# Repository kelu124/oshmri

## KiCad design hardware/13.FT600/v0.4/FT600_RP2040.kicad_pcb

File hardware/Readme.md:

# OSHMRI

## Concept

## Design

* [Source files](common_board/)

## PMODs specs

### AFE #1 (ADC)

* 1 dual PMOD, 12ADCbits+1clk + 1SPI (without MISO): based on the AD8331+ADC+DAC from https://github.com/kelu124/lit3rick/ (altium source in hardware folder) . Connector in: SMA, with MD0100 to protect. Possible elements:
  * AD8331
  * ADC: AD9629BCPZ-65: 12bits,
  * DAC: MCP4812-E/MS

### Ultrasound PULSER

* Only logic through PMOD: 
  * positivepulse, negativepulse, damp.
  * Expose remaining IOs on a 2.54" rail on the PMOD board (with 3.3V and GND as well)
* External GPIOs for +HV, -HV, GND. 
* Internal : 
  * Positive: 3.3V -> 5V booster ; 
  * Negative: -5V rail for example (not mandatory if simpler exists) https://www.mouser.fr/new/texas-instruments/ti-lm27761-voltage-inverter/
  * Design similar to the HV connector on lit3rick (jumpers to connect 5V to HV and -5V to -HV 
* Connector out: SMA.
* Ref design : https://www.arrow.com/en/reference-designs/high-voltage-pulser-circuit-using-the-md1213-and-tc6320-100v-ultrasound-pulser/4e167e0bac7f3ae2900d35260e7663cc 

### GRADIENTS PMOD

* Objective is to be able to produce 4 waveformes similar to those: https://github.com/kelu124/oshmri/tree/main/hardware#gradients
* 4 DACs outputs, 10bits (or more) : https://www.analog.com/media/en/technical-documentation/data-sheets/ltc2634.pdf
* there are already schematics and altium sources at
https://www.mouser.fr/ProductDetail/Analog-Devices/DC1488A-A?qs=ytflclh7QUXpxdBLSaXWCQ%3D%3D ( the only thing would be for outputs to be between -Vref and +Vref - using possibly a max1721 for neg. 3.3v ).

### !! NOT FOR THIS ONE - AFE #2 (SDR)
* Using the SDR chips: https://pbs.twimg.com/media/FLk5M53XsAIO2Jr?format=jpg&name=large path for 0-30MHz - IOs on the PMOD would be IO0..3 and the 4 SPI signals (for the DAC coupled to AD8331)
* Input as SMA, going to MD0100, AD8331, then MSI001, MSI2500, usb output.

# Specs

## Overview

The basic schematic of an MRI system is shown in Figure 1. The MRI spectrometer is responsible for playing out the RF and gradient pulses and receiving the MR signal and manages logic signals.

Overall strategy is: First make it work, then make it nice (=cheaper & more open source). 

Low cost (500eur) design for educational purposes and low budget. 3 typical freqs:

* 0.05 T - central freq 2.15MHz, 20kHz to 50kHz bandwidth
* 0.1  T - central freq 4 MHz, up to 500kHz bandwidth
* 0.3  T - central freq 13MHz, up to 500kHz bandwidth
* 0.5  T - central freq 21 MHz, up to 500kHz bandwidth

While it is definitely appealing to a have a broad application range for the spectrometer. An initial application goal would be DC-64MHz (up to B0=1.5T) or even lower. The first open source hardware MR systems will be low field (B0 inf to 0.5T, f~DC-21MHz). 

## Requirements

### Overall 

Maybe it's good for me to share what (hardware wise) the 'ideal' spectrometer requirements would look:

* 1xRF transmit channel - 16bit+
  * Voltage range: up to 1Vpp	
  * Sampling speed and nb bits: `@what@` -> _flexible_
  * Duration of transmit: up to 10ms, typically shorter.

#### Transmit

The minimum number of transmission channels is four (1x Tx RF, 3x Gradients). Is a higher number (how many?) in transmission channels desirable? e.g. for:
* broad BW excitation
* spatial encoding

* 4x kHz gradients transmits - (~250 kHz) ~20 bit dacs for the gradient waveforms
  * 4 SPIs ?

#### Receive

* 1x RF receive - Central freq @2, 4, 13 or 21Mhz. 
  * _BW on the Rx side nice-to-have would be 500 kHz, practically I think 50 kHz would satisfy most needs_
  * ADC 16bit 
  * Duration of acquisition : up to 20ms
  * Gain for acquisition : 0 to 30dB
* Ability to daisy chain for multiple receive channels (up to e.g. 16 or 32 RX channels would be great in the future to get an SNR boost)
* High frequency and phase stability (accurate and stable timings below 1us (preferably much less) jitter). One of the most important things in MR is the timing, both for transmission and reception (please check the IPSO part of the bruker hardware manual that I have attached). 

A higher number of receive channels increases SNR. 16-32 receive channels desirable.

### ADC

The bit depth varies on the SNR that is expected. With a human extremity low field system of 50 mT 14 bits for raw signal may be a good start. On the opposite side of the range, I have seen high field systems using 20 bits demodulated signal.

### IOs

GPIO pins to communicate with peripherals for for instance amplifier deblanking. Logic:
* Blanking
* Sampling on
* Gradients On
* Pulse On

### Other ports ?

* USB port 
* Ethernet port
* HDMI/VGA  Displayportport (HDMI/VGA)
* GPIO port
* Motor interface
* Debug Port (Rs232/422)
* PCI?
* SFP ports (Might be overkill but for the mid cost version, it can boost many operations. Also, low cost versions can be used for the slower communications/instructions when interfacing between imaging room and the spectrometer)

## Storage

* Images are 256x256*256 or above, 16bits imaginary
  * 64MB / image
  * 256kB / plane

## Ideas

PMODs! 8 IOs = loads

* Transmit: AD9102 - 20 EUR
  * 14 bits, 180Msps, 4096 word pattern
  * @180msps, 4096pts = 22us.

## RF

### Overall

On the RF image, green represents acquisitions. Do you confirm that's for the 3 ADCs?

I agree that might be a bit confusing. Green is not the acquisition, it is the gradient. There are three gradients for different purposes and the acquisition (sampling) is in between two gradients (orange and green in TSE sequence description.png)) and during x gradient (blue) at 10ms, 20ms, 30ms etc. This is a single line of the MR image and this pulse sequence is being repeated multiple times (e.g. 128 or 256). The lengths of the pulse sequence is called TR repetition time. A better understanding is here (check fast spin echo and the signal location, thats where ADC sampling kicks in). There is only one ADC for sampling the receiving signal per RF receive coil channel. One thing that is being done and that boost SNR is to have multiple RF receiver channels. Thats why my previous comment to have an option to add or connect more Rx channels later would be great. For transmission at the moment 1 RF channel is sufficient. More would be interesting, but more from research perspective and at the moment 1 is sufficieent. For the gradients we need 3Tx. Forget about the 64MHz for the moment (we dont have 1.5T magnets for the OSH stuff anyway at the moment) if its too complicated, we can focus on the low field MR systems up to 0.5T (So in total 1xRF @ 1 or 2MHz - 22MHz. ven up to 0.2T or 0.3T, ca 13MHz would be fine).

### Gradients

## Blocks

### RF acquisitions

* And how long does it take? I'm reading roughly 10ms acquisitions. _The sinc pulse that is shown is for transmission, which is around 10ms. They can be also shorter. For the acquisition it will be typically shorter (e.g. in the TSE sequence image that I have sent you it is around 5ms, but it could be higher e.g. 20ms (see also docs from answer below))_
* At 64Msps that's quite some data (64*10*1000 points). _Yes MRI scans produce quite some data, but there are also some tricks. Have a look here: http://mri-q.com/receiver-bandwidth.html and here: [bandwidthinmrisiemens.pdf](pdfs/bandwidthinmrisiemens.pdf)._

### Gradients

* On the gradient waveforms, do you confirm that's more or less constants (ie square pulses)? _The gradient waveforms are mostly trapezoidal. There are some more fancy things with arbitrary gradient waveforms, but for classical MR that would be ok._

### Block pulses

* I trust the Block pulse is a gate pulse - what is its lengths? A ms or so ? _There will be a pulse to gate the RF power amplifier and the TR switches. The pulse lengths depends on the RF pulse lenghts. So sth like 1-5ms._

## Competition

'It has shortcomings too. I think one of the reasons we've decided to work with it now is that it is being adopted across multiple sites so that the development burden is shared.'

## To sort

* Thesis for the development of a https://upcommons.upc.edu/handle/2117/90394?locale-attribute=en FT600 +SDR
   * https://www.maximintegrated.com/en/products/analog/data-converters/analog-front-end-ics/MAX5866.html

* AD8339 better ? DC to 50MHz

## Ideas:

#### Core PMODs

* Board central + extesions
  * xPMOD DAC for pulse (MRI)
  * 1PMOD for pulse (ultrasound)
  * 2PMOD ADC for acquisition - onboard + gain -- common
  * 1PMOD 4 Gradients (MRI)
  * 1PMOD for HV (ultrasound + external alim)
* Comm
  * 2PMOD for USB3: FT600
  * 2PMOD for USB3: CH569
* Comm output:
  * Msi001 Msi2500 for USB

#### Backlog for PMODS

* __ACQ__: 1 dual PMOD, 12ADCbits+1clk + 1SPI (without MISO): based on the AD8331+ADC+DAC from https://github.com/kelu124/lit3rick/ . Connector in: SMA, with MD0100 to protect.
* __USPULSE__: 1 single PMOD: for the concept here: https://www.arrow.com/en/reference-designs/high-voltage-pulser-circuit-using-the-md1213-and-tc6320-100v-ultrasound-pulser/4e167e0bac7f3ae2900d35260e7663cc . Only logic through PMOD. External GPIOs for +HV, -HV, GND. Connector out: SMA.
* __4GRADs__ 1 PMOD: 4 DACs outputs, 10bits (or more) to start with. MCP48CMB24-E/ML could work, maybe? Objective is to be able to produce 4 waveformes similar to those: https://github.com/kelu124/oshmri/tree/main/hardware#gradients
* __SDR ACQ__: https://pbs.twimg.com/media/FLk5M53XsAIO2Jr?format=jpg&name=large path for 0-30MHz - IOs on the PMOD would be IO0..3 and the 4 SPI signals (for the DAC coupled to AD8331) Input as SMA, going to MD0100, AD8331, then MSI001, MSI2500, usb output.

## Competition

Commercially available spectrometers (>2000€)
* Kea 2	
* Crimson TNG	
* EVO	
* Redstone	
* iSpin-NMR	
* Medusa	
* Pure Devices	
* TekMag	
* RS2D	
* Ettus USRP SDR
*  Aspect Imaging – AMOS

## Pulser

## Resources:

## First set

* https://www.researchgate.net/publication/232935201_A_digital_receiver_module_with_direct_data_acquisition_for_magnetic_resonance_imaging_systems
  * AD9852 DDS + direct sampling
* https://www.researchgate.net/publication/231108694_A_single-board_NMR_spectrometer_based_on_a_software_defined_radio_architecture
* https://www.researchgate.net/publication/51189854_A_versatile_pulse_programmer_for_magnetic_resonance_imaging
* https://www.researchgate.net/publication/265176277_Comparison_of_Analog_and_Digital_Transceiver_Systems_for_MR_Imaging

## Other

* Liang X, A digital magnetic resonance imaging spectrometer using digital signal processor and field programmable gate array. DOI: 10.1063/1.4803007
* Takeda K, A highly integrated FPGA-based nuclear magnetic resonance spectrometer, DOI: 10.1063/1.2712940
* Zhao C, Design of a digital spectrometer for the MRI system, PMID: 17672364
* Hasselwander, Christopher J., Zhipeng Cao, and William A. Grissom. "gr-MRI: A software package for magnetic resonance imaging using software defined radios." Journal of Magnetic Resonance 270 (2016): 47-55.
* Layton, Kelvin J., et al. "Pulseq: A rapid and hardware‐independent pulse sequence prototyping framework." Magnetic resonance in medicine 77.4 (2017): 1544-1552.
* Ravi, Keerthi Sravan, et al. "Pulseq-Graphical Programming Interface: Open source visual environment for prototyping pulse sequences and integrated magnetic resonance imaging algorithm development." Magnetic resonance imaging 52 (2018): 9-15.

# Software reqs

There are a couple of existing possibilities to enable this:
* Python based backend programming. 
* Extend Pulseq framework Ref, then GPI Ref or other higher level sequence programming packages can be used for easy programming of pulse sequences. 
* Compatibility with gnuRadio (https://www.gnuradio.org/), then the grMRI framework can be used and extend to program pulse sequences Ref. 

# Qui ?

* Lukas W
* Lionel B
* Tom OR

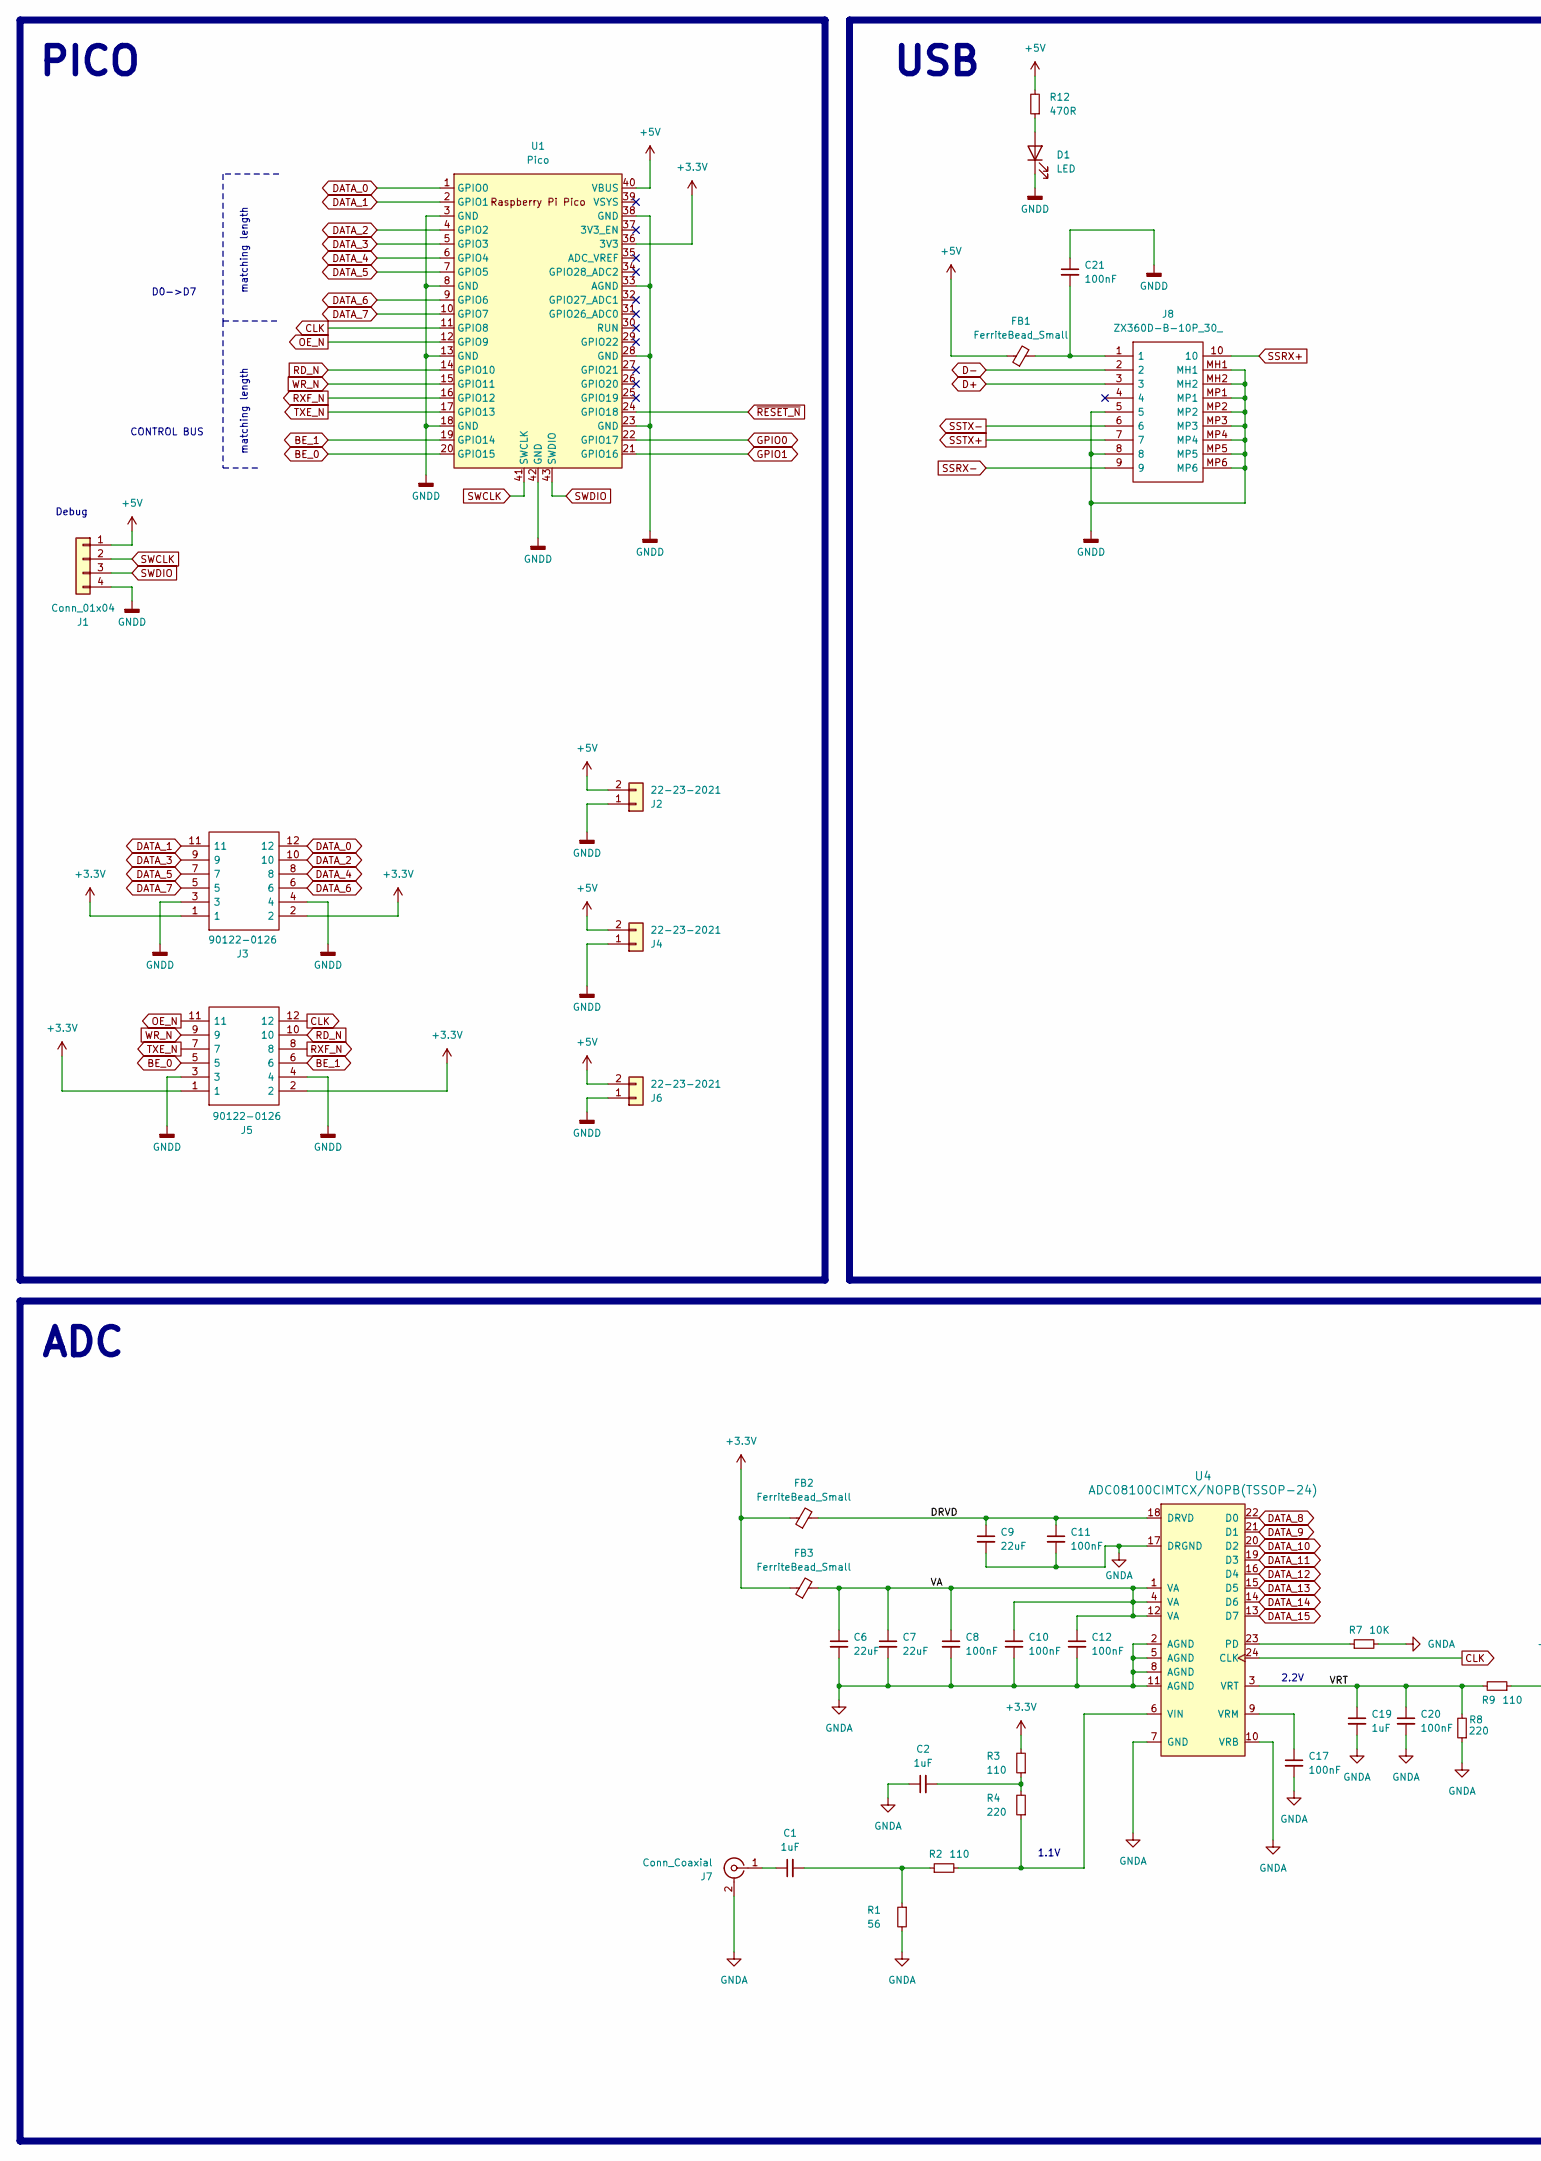
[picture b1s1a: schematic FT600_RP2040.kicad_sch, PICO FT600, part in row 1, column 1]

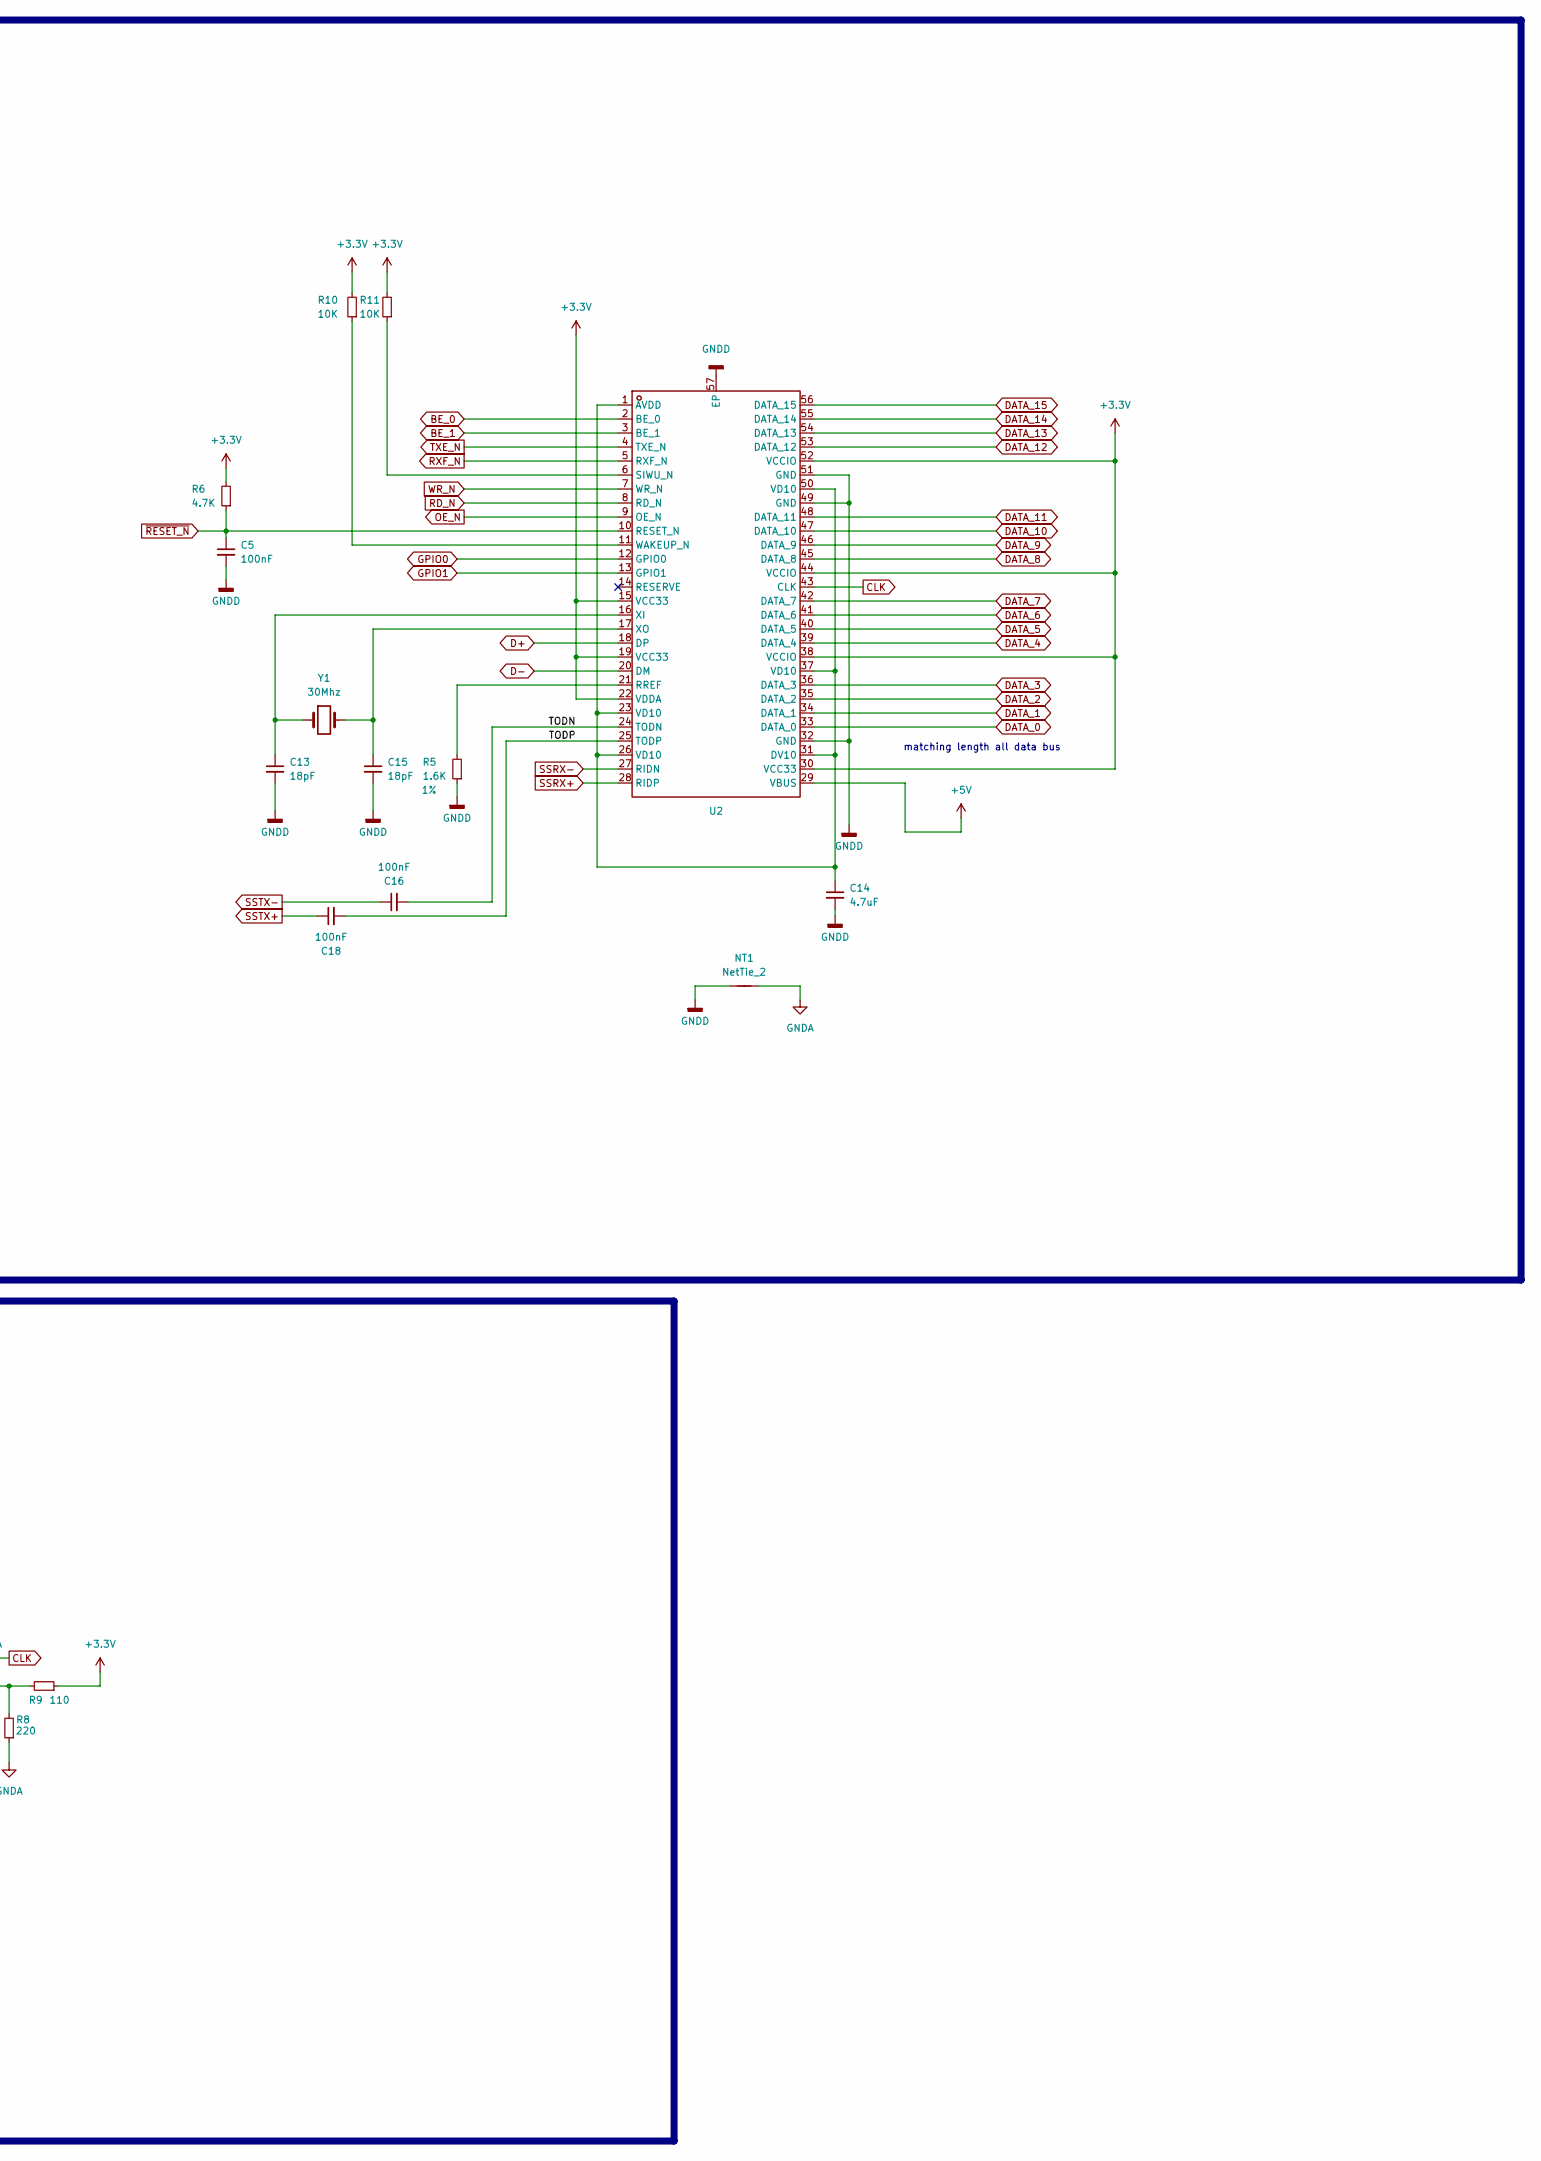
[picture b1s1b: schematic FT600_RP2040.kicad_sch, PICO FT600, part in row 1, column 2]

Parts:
C1, C2, C19: 1uF; C_1206_3216Metric
C5, C8, C10, C11, C12, C16, C17, C18, C20, C21: 100nF; C_1206_3216Metric
C6, C7, C9: 22uF; C_1206_3216Metric
C13, C15: 18pF; C_1206_3216Metric
C14: 4.7uF; C_1206_3216Metric
D1: LED; LED_0805_2012Metric
FB1, FB2, FB3: FerriteBead_Small; L_1206_3216Metric
J1: Conn_01x04; PinHeader_1x04_P2.54mm_Vertical
J2, J4, J6: 22-23-2021; PinHeader_1x02_P2.54mm_Vertical; MPN 22-23-2021
J3, J5: 90122-0126; PinSocket_2x06_P2.54mm_Horizontal; Mouser Part Number 710-613012243121
J7: Conn_Coaxial; AMPHENOL_132357-11
J8: ZX360D-B-10P_30_; ZX360DB10P30; Mouser Part Number 798-ZX360D-B-10P30
NT1: NetTie_2; NetTie-2_SMD_Pad2.0mm
R1: 56; R_1206_3216Metric
R2, R3, R9: 110; R_1206_3216Metric; Tolerance 1%
R4, R8: 220; R_1206_3216Metric; Tolerance 1%
R5: 1.6K; R_1206_3216Metric; Tolerance 1%
R6: 4.7K; R_1206_3216Metric; Tolerance 1%
R7: 10K; R_1206_3216Metric
R10, R11: 10K; R_1206_3216Metric; Tolerance 1%
R12: 470R; R_1206_3216Metric; Tolerance 1%
U1: Pico; RPi_Pico_SMD; MPN Pico
U2: FT600Q-B-T; Manufacturer Part FT600Q-B-T; LCSC Part Name FT600Q-B-T
U4: ADC08100CIMTCX/NOPB(TSSOP-24); TSSOP-24_4.4x7.8mm_P0.65mm
Y1: 30Mhz; Crystal_SMD_Abracon_ABM7-2Pin_6.0x3.5mm; Tolerance 20ppm; MPN ABM7-30.000MHZ-D2Y-T

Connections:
+3.3V: FB2.1, FB3.1, J3.1, J3.2, J5.1, J5.2, R3.2, R6.2, R9.1, R10.2, R11.2, U1.36 (3V3), U2.15 (VCC33), U2.19 (VCC33), U2.22 (VDDA), U2.30 (VCC33), U2.38 (VCCIO), U2.44 (VCCIO), U2.52 (VCCIO)
+5V: FB1.1, J1.1, J2.2, J4.2, J6.2, R12.2, U1.40 (VBUS), U2.29 (VBUS)
/DRVD: C9.1, C11.1, FB2.2, U4.18 (DRVD)
/TODN: C16.2, U2.24 (TODN)
/TODP: C18.2, U2.25 (TODP)
/VA: C6.1, C7.1, C8.1, C10.1, C12.1, FB3.2, U4.1 (VA), U4.4 (VA), U4.12 (VA)
/VRT: C19.1, C20.1, R8.2, R9.2, U4.3 (VRT)
BE_0: J5.5, U1.20 (GPIO15), U2.2 (BE_0)
BE_1: J5.6, U1.19 (GPIO14), U2.3 (BE_1)
CLK: J5.12, U1.11 (GPIO8), U2.43 (CLK), U4.24 (CLK)
D+: J8.3, U2.18 (DP)
D-: J8.2, U2.20 (DM)
DATA_0: J3.12, U1.1 (GPIO0), U2.33 (DATA_0)
DATA_1: J3.11, U1.2 (GPIO1), U2.34 (DATA_1)
DATA_2: J3.10, U1.4 (GPIO2), U2.35 (DATA_2)
DATA_3: J3.9, U1.5 (GPIO3), U2.36 (DATA_3)
DATA_4: J3.8, U1.6 (GPIO4), U2.39 (DATA_4)
DATA_5: J3.7, U1.7 (GPIO5), U2.40 (DATA_5)
DATA_6: J3.6, U1.9 (GPIO6), U2.41 (DATA_6)
DATA_7: J3.5, U1.10 (GPIO7), U2.42 (DATA_7)
DATA_8: U2.45 (DATA_8), U4.22 (D0)
DATA_9: U2.46 (DATA_9), U4.21 (D1)
DATA_10: U2.47 (DATA_10), U4.20 (D2)
DATA_11: U2.48 (DATA_11), U4.19 (D3)
DATA_12: U2.53 (DATA_12), U4.16 (D4)
DATA_13: U2.54 (DATA_13), U4.15 (D5)
DATA_14: U2.55 (DATA_14), U4.14 (D6)
DATA_15: U2.56 (DATA_15), U4.13 (D7)
GNDA: C2.1, C6.2, C7.2, C8.2, C9.2, C10.2, C11.2, C12.2, C17.2, C19.2, C20.2, J7.2 (Ext), NT1.2, R1.2, R7.2, R8.1, U4.2 (AGND), U4.5 (AGND), U4.7 (GND), U4.8 (AGND), U4.10 (VRB), U4.11 (AGND), U4.17 (DRGND)
GNDD: C5.2, C13.2, C14.2, C15.2, C21.1, D1.1 (K), J1.4, J2.1, J3.3, J3.4, J4.1, J5.3, J5.4, J6.1, J8.5, J8.8, J8.MH1, J8.MH2, J8.MP1, J8.MP2, J8.MP3, J8.MP4, J8.MP5, J8.MP6, NT1.1, R5.1, U1.3 (GND), U1.8 (GND), U1.13 (GND), U1.18 (GND), U1.23 (GND), U1.28 (GND), U1.33 (AGND), U1.38 (GND), U1.42 (GND), U2.32 (GND), U2.49 (GND), U2.51 (GND), U2.57 (EP)
GPIO0: U1.22 (GPIO17), U2.12 (GPIO0)
GPIO1: U1.21 (GPIO16), U2.13 (GPIO1)
unnamed: C1.2, R1.1, R2.1
unnamed: C2.2, R3.1, R4.2
unnamed: C21.2, FB1.2, J8.1
unnamed: D1.2 (A), R12.1
unnamed: C1.1, J7.1 (In)
unnamed: C14.1, U2.1 (AVDD), U2.23 (VD10), U2.26 (VD10), U2.31 (DV10), U2.37 (VD10), U2.50 (VD10)
unnamed: R5.2, U2.21 (RREF)
unnamed: R11.1, U2.6 (SIWU_N)
unnamed: R10.1, U2.11 (WAKEUP_N)
unnamed: C13.1, U2.16 (XI), Y1.1
unnamed: C15.1, U2.17 (XO), Y1.2
unnamed: R7.1, U4.23 (PD)
unnamed: R2.2, R4.1, U4.6 (VIN)
unnamed: C17.1, U4.9 (VRM)
OE_N: J5.11, U1.12 (GPIO9), U2.9 (OE_N)
RD_N: J5.10, U1.14 (GPIO10), U2.8 (RD_N)
RXF_N: J5.8, U1.16 (GPIO12), U2.5 (RXF_N)
SSRX+: J8.10, U2.28 (RIDP)
SSRX-: J8.9, U2.27 (RIDN)
SSTX+: C18.1, J8.7
SSTX-: C16.1, J8.6
SWCLK: J1.2, U1.41 (SWCLK)
SWDIO: J1.3, U1.43 (SWDIO)
TXE_N: J5.7, U1.17 (GPIO13), U2.4 (TXE_N)
WR_N: J5.9, U1.15 (GPIO11), U2.7 (WR_N)
~RESET_N: C5.1, R6.1, U1.24 (GPIO18), U2.10 (RESET_N)

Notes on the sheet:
ADC
CONTROL BUS
USB
matching length
2.2V
PICO
1.1V
Debug
matching length all data bus
D0->D7

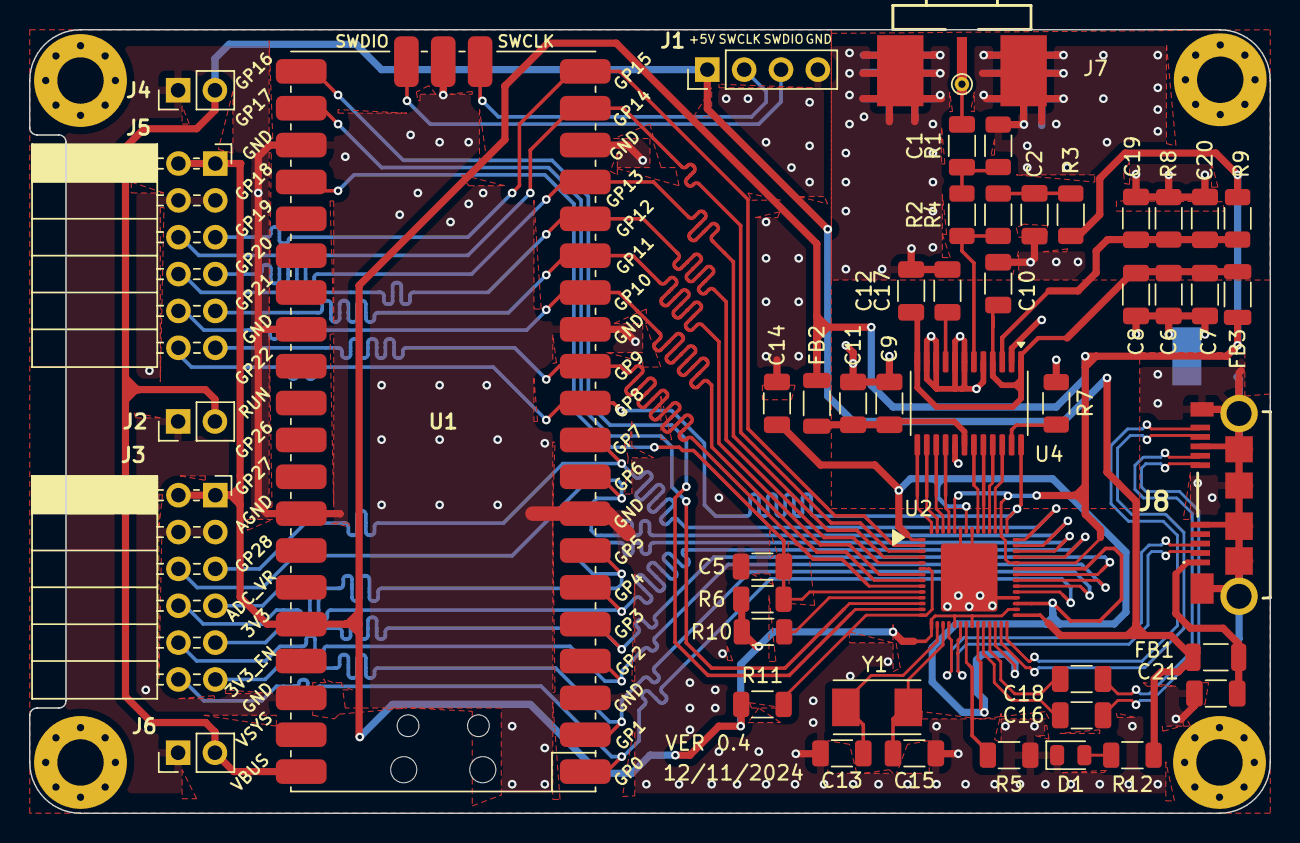
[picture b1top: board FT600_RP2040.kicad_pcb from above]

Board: 2 copper layers, 85.5 x 54.0 mm, 48 parts (1 on the bottom side), 58 nets.

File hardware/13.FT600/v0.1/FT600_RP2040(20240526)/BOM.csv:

"Reference","Value","Footprint","Tolerance","MPN","Qty","Package"
"C1,C2,C19","1uF","Capacitor_SMD_AKL:C_1206_3216Metric","","","3","1206"
"C5,C8,C10,C11,C12,C16,C17,C18,C20,C21","100nF","Capacitor_SMD_AKL:C_1206_3216Metric","","","10","1206"
"C6,C7,C9","22uF","Capacitor_SMD_AKL:C_1206_3216Metric","","","3",""
"C13,C15","18pF","Capacitor_SMD_AKL:C_1206_3216Metric","","","2","1206"
"C14","47uF","Capacitor_SMD_AKL:C_1206_3216Metric","","","1","1206"
"FB1,FB2,FB3","FerriteBead_Small","Inductor_SMD_AKL:L_1206_3216Metric","","","3","1206"
"IC2","FT600Q-B-T","ICTAMKY_V8:FT600Q-B-T","","","1",""
"J1","Conn_01x04","Connector_PinHeader_2.54mm:PinHeader_1x04_P2.54mm_Vertical","","","1",""
"J2,J4,J6","22-23-2021","Connector_PinHeader_2.54mm:PinHeader_1x02_P2.54mm_Vertical","","22-23-2021","3",""
"J3,J5","90122-0126","Connector_PinSocket_2.54mm:PinSocket_2x06_P2.54mm_Horizontal","","90122-0126","2",""
"J7","Conn_Coaxial","ICTAMKY_V8:AMPHENOL_132357-11","","","1",""
"J8","ZX360D-B-10P_30_","SamacSys_Parts:ZX360DB10P30","","","1",""
"R1","56","Resistor_SMD_AKL:R_1206_3216Metric","","","1",""
"R2,R3,R9","110","Resistor_SMD_AKL:R_1206_3216Metric","1%","","3","1206"
"R4,R8","220","Resistor_SMD_AKL:R_1206_3216Metric","1%","","2","1206"
"R6","4.7K","Resistor_SMD_AKL:R_1206_3216Metric","1%","","1","1206"
"R7","10K","Resistor_SMD_AKL:R_1206_3216Metric","","","1",""
"U1","Pico","ICTAMKY_V8:RPi_Pico_SMD","","Pico","1",""
"U4","ADC08100CIMTCX/NOPB(TSSOP-24)","Package_SO:TSSOP-24_4.4x7.8mm_P0.65mm","","","1",""
"Y1","30Mhz","Crystal:Crystal_SMD_Abracon_ABM7-2Pin_6.0x3.5mm","20ppm","ABM7-30.000MHZ-D2Y-T","1",""
